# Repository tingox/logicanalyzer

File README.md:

# LogicAnalyzer

test 

## Downloads
You can find all the compiled projects in the [Releases section](https://github.com/gusmanb/logicanalyzer/releases).

Latest version: Release 5.1.0.0, 05/05/2024
----

# More boards on the go!

One of the new functionalities of the RP2350 is the capability of having two XIP devices and also has the full device implementation (RP2040 only had READ capabilities implemented). This means that is possible to have (for example) a flash device *and* a PSRAM connected to it.
Unfortunatelly the Pico 2 does not expose the QSPI pins and they are tied directly to the flash... But there is hope! PiMoroni has developed the PiMoroni Pico Plus 2 which contains 16Mb of flash and 8Mb of PSRAM.

I already have ordered one of these new boards and have some ideas on what could be done with them :D
Right now the most possible one is this: PSRAM is not fast enough for sampling at a decent speed with many channels, BUT, it is fast enough for something like storing ADC samples, so what I'm going to try is to allow the mix of analog and digital channels. The analog channels will be very slow compared to the digital ones (only 500Ks/s) but it still can be useful to monitor behaviors of things like motors, servos or whatever. As the PSRAM is 8Mb it will allow to store up to 8 seconds of analog data on single channel mode (2 bytes per sample at 500Ks/s is roughly 1Mb/s of data), this, combined with the upgraded onboard ram and the burst mode can be really useful in multiple projects.

Stay tuned for more news!

----

# Exciting news! The Pico 2 is coming soon!

As some of you may know the Pico 2 is being released this month. The new Pico 2 is a very exciting upgrade of the pico, more powerful cores, two alternative RiscV cores, three PIO units instead of two and 520Kb of RAM!

This can be a game changer for LogicAnalyzer, only with the new ammount of RAM the quantity of samples is going to increase massively, we're talking about three times the current ammount of samples!

Also, there are really exciting changes on the PIO side, the new IRQ system allows to intercomunicate the PIO units, this means that the trigger pins could be freed now, and this, as small change as it seems can be really amazing combined with the new third PIO unit... Think about this, a 64Mb dual SPI RAM running at 100Mhz connected to the two free pins and controlled at full speed by the third PIO unit... 

I was preparing a release for this month but it's going to be delayed, once I receive the new Pico's I will start the development for the Pico 2 and once it's completed I will release all at once.

Stay tuned!

## RELEASE 5.1

This release is a QoL release with some functional corrections. For more details check the release page.

## RELEASE 5.0, Burst mode is here!

New release with exciting feature!

The biggest change on this release is the Burst mode. With burst mode you can capture blocks of data and the analyzer will rearm itself immediatelly and capture more data when the trigger condition is met again. This will improve the memory usage discarding unneeded samples! Right now only the simple trigger mode accepts burst mode but in a future I will try to implement it in all the other triggers.
For more information check [the wiki.](https://github.com/gusmanb/logicanalyzer/wiki/06---The-LogicAnalyzer-program#triggers)

Also new features to ease the navigation in the capture viewer have been added like shortcuts and a preview of the full capture. More info in [the wiki.](https://github.com/gusmanb/logicanalyzer/wiki/06---The-LogicAnalyzer-program#navigating-on-the-capture-viewer)

Finally multiple improvements have been done, some bugs in the capture tail detection have been corrected, the USB transfer has been improved using directly the CDC transfer functions and more.

Beware that this version is not compatible with other ones, the protocol has changed. The driver will check the device version and will not connect to it if it is lower than V5.0.

Have fun!

----

## UPDATE 28/06/2023 - Release 4.5.1 - QOL improvements

This release include some QOL updates to the applications.

LogicAnalyzer app:

* Ammount of on-screen samples will be preserved if you repeat the last capture.
* Added a new menu entry called "Repeat las analysis" to the protocol analyzers, it will execute the last analysis performed to speed up things.
* Changed where config files are stored, they will use the %appData% folder now ($home/.config in Linux).
* Changed horizontal scrollbar visibility.

CLCapture app:

* Now channel names can be provided from the command line.

Have fun!

----

## UPDATE 11/04/2023 - Release 4.5 - Support for the RP2040-Zero and new board definition system

This release includes only an update to the firmware.

First, the RP2040-Zero is now officially supported (no shifter board for it though). 
You can download the firmware for it on the [releases](https://github.com/gusmanb/logicanalyzer/releases) section. Also, the pinout has been added to the [wiki](https://github.com/gusmanb/logicanalyzer/wiki/02---LogicAnalyzer-Hardware#barebones-configuration) so you can use it with the bare-bones configuration.

And second, the firmware has been refactored in order to make a lot easier to add new boards. You have the complete instructions on how to add support to a new board on [the wiki firmware section](https://github.com/gusmanb/logicanalyzer/wiki/03---LogicAnalyzer-Firmware). Also, as some boards include the very popular WS2812 RGB led the firmware includes a driver for it, it's purely software-based, no timers nor interrupts needed, so feel free to use it if you want.

If you add support for a new board, feel free to create a pull request with the changes :)

Have fun!

----

## UPDATE 25/02/2023 - Release 4.0 is up! Channels a go-go!

Hi again! This is a BIG update loaded with new functions and improvements to the hardware, firmware and software!

Let's start with the little things: we have a logo! Yes, it's nothing important but I hated to not to have a proper one so I designed one that I think fits well to the project :D

Next, we have a proper Wiki! All the project has been documented: hardware, firmware and software. If you have any doubt check it as I have tried to explain everything related to the analyzer usage in there. If you find any error or missing feature please open an issue and I will correct it as soon as I can.

Ok, now the changes to the hardware. There is a new pcb for the analyzer that includes two connectors to daisy chain the analyzers. You can use two or three Dupont wires (the central pin is unused, it's reserved for future usage, I have left it there so anyone that produces these PCB's can patch them easily).

And the firmware has also been updated to support the daisy chaining. So, what is for the daisy chaining? Well, daisy chaining allows to chain up to five analyzers without wasting pins so you now will be able to capture a massive ammount of **120 CHANNELS!!!** Check the [Connection](https://github.com/gusmanb/logicanalyzer/wiki/06---The-LogicAnalyzer-program#connecting-to-devices) and [Capture](https://github.com/gusmanb/logicanalyzer/wiki/06---The-LogicAnalyzer-program#capture) sections of the Wiki to know all the possibilities and how to use them.

Now, the software. It contains many changes, so I'm going to start with the improvements and then with the new functionalities.

First I have improved the sample rendering. It is now more visible and looks a lot better. Also, the guides shown to see where a sample starts and ends are automatically scaled or removed, it made no sense to have so many lines that they made a solid gray background, so when there are too many they will get automatically deactivated. Also, this allowed to improve the performance so now the sample viewer will allow to show up to 2000 samples in screen without any check.

Related to this the protocol analyzer renderer has been updated, it will take less useless space and will hide the information if it does not fit in the assigned space.

Now, the connection system has been updated to include a "multidevice", this is the device that you must use when using the daisy chained analyzers.

Next, the capture dialog has been updated, the mode selector has been removed and the mode is autoselected based in the channels enabled, check the [Wiki page](https://github.com/gusmanb/logicanalyzer/wiki/06---The-LogicAnalyzer-program#basic-parameters) to know the limits and modes.

Also, the capture dialog has a new channel selector, more visual and that includes the name field for the channels, instead of configuring the names after the capture has been finished (and lose these if you capture again) the names can be entered directly on the capture dialog. These names will be preserved between captures (and if you change them from the channel viewer these changes will be respected).

This new channel selector also allows to show up to the 120 channels that can be used when daisy chaining five devices, the selector will have a scrollbar when the channel list is bigger than its space.

Another change, the editing features have been improved and expanded. First of all, you will not need to create regions to execute edit actions, the sample range selection has been improved and it is used now for these. Check the [Wiki page](https://github.com/gusmanb/logicanalyzer/wiki/06---The-LogicAnalyzer-program#editing-captures) to see a description on how it works and which new features have been included.

Finally, the system now can create capture files from scratch, for this I have implemented a language that allows to describe signals in an easy way, it even includes a colored syntax editor, check the [Wiki](https://github.com/gusmanb/logicanalyzer/wiki/06---The-LogicAnalyzer-program#the-signal-description-language) for a description of this language!

Also, I already have planned the next update, I'm not sure when it will be ready but I will implement it for sure, and this is one of the motivations to create the SDL language: replay captures! ;)

This is a resume of the most prominent changes, surely that I forgot some, but all are documented in the Wiki, so ensure to review it!

Any feedback about the update will be welcome, so don't hesitate to open issues or start discussions.

Have fun!

## UPDATE 07/02/2023 - New release with updated shared driver.

This is a bug-fix release, with the introduction of the Pico-W WiFi support I unified the transfer mode in the driver using streams for network and for the serial port, but I forgot that .net 6.0 Ports package causes problems with Linux, so the previous release will hung the app when receiving more than 4k samples... Doh!

I have updated the code to use the same work around that I used previously and the problem has been fixed.

Have fun!

----

## UPDATE 04/02/2023 - New release! Bugs corrected and more samples!

Hi! This update comes loaded of news.

### First of all, bug corrections. 

The biggest bug that has been corrected is the fast trigger in the Pico-W. When I implemented the Pico-W I tried it extensively, but I used only the simple trigger to do the tests. What was my surprise when I tried to use the Pico-W with a fast trigger and I found that it got completelly hung!

The thing is that the Pico-W hides a little secret that I haven't found documented anywhere, this little secret is that the driver uses a PIO program to do the transfers! The fast trigger uses a full PIO unit, all its 32 instructions to create a jump table, and the CYW driver uses a SM in the PIO1 to do the SPI transfers. So I tried to swap the PIO units and it at least started to capture, but the capture was never finished, I have revised up-to-down the driver and still haven't found why the PIO1 interrupts don't work at all after the CYW driver has been enabled, so I have done a work-around that does not need the IRQ to trigger a handler. So, if you are using a Pico-W update the firmware asap.

The next bug is a small bug that caused that some samples weren't clear correctly when a trigger was rised immediately after starting capture (for example the trigger condition is already met when the first sample is done).

### And now, the really big news, MORE SAMPLES!

I have tweaked the buffer transference between the PIO and the memory and it allows to hold up to 131071 samples! Of course this is at the expense of how many channels you use, the device now has three modes: 8 channels, 16 channels and 24 channels.

The sample limits are specified here:

 * Mode 8:
 
     * Minimum pre-samples: 2
     * Maximum pre-samples: 98303
     * Minimum post-samples: 512
     * Maximum post-samples: 131069
     * Maximum total samples: 131071
     
 * Mode 16:
 
     * Minimum pre-samples: 2
     * Maximum pre-samples: 49151
     * Minimum post-samples: 512
     * Maximum post-samples: 65533
     * Maximum total samples: 65535
     
 * Mode 24:
 
     * Minimum pre-samples: 2
     * Maximum pre-samples: 24576
     * Minimum post-samples: 512
     * Maximum post-samples: 32765
     * Maximum total samples: 32767

As you can see, using the 8 channel mode you can capture up to four times the samples that were available until now, a substantial increase.
The channels used for 8 and 16 modes must be the first ones, you cannot choose eight random channels, and this introduces a limitation, they collide with the complex and fast triggers (not the simple trigger, for that you still can use any channel left). Bear in mind this to plan how you configure your capture, for example for the 8 channel mode you still can have a 8 channel complex trigger or a fast 5 channel trigger without including these channels in the capture, but if you need more channels for one of these triggers, or you need to use the 16 channel mode you will suffer of this.

### Another new update, now you can show up to 1024 samples in screen!

You can activate this feature from the main screen, it has a checkbox (which will warn you as this may be a very CPU intensive task for old computers) that allows you to change the on-screen samples from 200 to 1024, this is really useful for use with big screens and modern computers.

Also I have tweaked a bit the appearance of the sample viewer, I didn't liked the dashed lines so now all are continuous ones.

Well, that's it for now.

Have fun!

----

## UPDATE 03/02/2023 - Measurement tool.

This is a very handy update to the analyzer, you can measure a region and get information of each channel: total samples selected, period of the selection, number of positive pulses, number of negative pulses, average and predominant period for positive and negative pulses and average and predominant frequency.

The predominant values are calculated applying a variant of the 95th percentile rule to discard aberrant/broken samples and I must say it works really well, it matched exactly all the frecuencies I have tested.

There is still no new release, you will need to compile the application if you want it, but I will create the release very soon.

Have fun!

----

## UPDATE 02/02/2023 - I2C protocol analyzer.

New day, new analyzer :D. This time is the turn for I2C. The analyzer will show you the raw data, the ACK/NACK's and will also show the device address (7 and 10 bit modes), operation of a request and any kind of frame error. To install it get it from [here](https://github.com/gusmanb/logicanalyzer/blob/master/I2CProtocolAnalyzer.dll) and copy it to the "analyzers" folder of the application.

Have fun!

----

## UPDATE 01/02/2023 - Serial protocol analyzer.

This is a small update, I have created a serial protocol analyzer (RS-232). This update does not include a release but I have left the analyzer library compiled in the repository. To install it get it from [here](https://github.com/gusmanb/logicanalyzer/blob/master/SerialProtocolAnalyzer.dll) and copy it to the "analyzers" folder of the application.

It supports positive and negative polarity (for TTL and RS-232 level signals), two channels (RX + TX), 7 or 8 bits, no parity/odd parity/even parity and 1, 1.5 or 2 stop bits.

Have fun!

----

## UPDATE 31/01/2023 - Pico-W support and WiFi!

It's finally here! WiFi support!

First of all, there are now three different firmware versions in the release section, one with no suffix for the regular pico, another with the "W" suffix for the Pico-W with no WiFi support and a final one with the "WIFI" suffix for the Pico-W with WiFi support. Choose the one that best suits your needs.

Now, how to use the WiFi support?

First of all, you need a Pico-W, I think that's obvious :D, flash it with the "WIFI" firmware and the device is ready to be used. If you plan to solder the Pico-W to the analyzer board beware to not to add the debug pins as they are now located in the middle of the board and it will not allow you to solder it, if you want them then you will need to use some pin headers to rise the Pico from the board (for my own device is what I always have done, in this way I can replace the Pico whenever I want).

Ok, now let's see how to use it.

First of all, you need to connect at least once the Pico-W to the computer to configure the network settings, this process can be done as many times as you want, connect the Pico-W to the computer and use the CLCapture or the LogicAnalyzer software to configure it.

When you connect the Pico-W with the WiFi firmware you will notice that a new menu gets enabled:

From there you can then select the "Update Network Settings" menu.

That will open the dialog to configure the network settings, you must enter the SSID of your router, the password (only WPA2 is supported), the desired static IP address and the listening TCP port.

Once these are configured accept them and they will be saved to the Pico-W flash, immediately the Pico-W will try to connect to your router, if it's available it will connect and it will be available for network connection.

To connect to the Pico-W through WiFi you must select from the dropdown menu the "Network" option.

Once you select it and press the "Open" button the network connection dialog will open.

Fill the IP address and port and press "Accept", if the device is available it will connect to it.

And that's it! From that point the device works exactly as before, for the application is indifferent if it is connected through network or USB, it has the exact same functionalities.

### The CLCapture updates

The CLCapture also supports the network connection and configuration, for that purpose now the command line starts with a verb, execute the program without any parameter to check the verbs and only with a verb to get the required parameters.

### Some notes

Both interfaces (USB and WiFi) work at the same time, but when a client gets connected through WiFi the USB will be ignored until the client gets disconnected, keep it in mind.

I have found some quirks on the Pico-W WiFi support, the first one is that it does not support at all to connect without a DHCP server, and it always gets the network information from there, fortunatelly I have found a way to change the IP address once it is connected to the AP. This also causes a problem (at least in my router), if you are already connected to the AP and you change the network settings the device disconnects from it and reconnects with the new info, if is the same AP (per example you have just changed the IP address) the static IP is ignored and it will retain the one assigned by the DHCP server, the solution is easy, restart the Pico-W and it will connect with the new IP address.

The firmware now has three "flavours" when compiled, this is controlled from the "LogicAnalyzer_Build_Settings.h" header and the "CMakeLists.txt" files, both contain instructions on how to change the settings based on your preferences.

A user adviced me that the Pico-W may have problems if the USB is connected to a host and the WiFi is used. I haven't experienced none of these and I have tested it extensively, maybe as I have used a sepparated core for the WiFi it avoids this kind of trouble, but if you experience them then use a USB power supply (like a phone charger or similar) if you want to connect through WiFi.

### The future

I'm thinking about creating a new PCB board that contains a battery and an USB charging module, in this way the device will become totally free of wires (except for the ones for the signals, obviously). I think this could be extremely useful, you will be able to place the analyzer even inside a computer or any kind of device and connect to it remotely, I think this could be extremely useful for devices that are in fixed places or are big and difficult to move (like old mini computers or car ECU's).

Stay tunned for more news, and be sure the project still is not completed!

Have fun!

----

## UPDATE 29/01/2023 - Software update

This release contains many updates to the GUI, CLI and driver and also includes many new target architectures.

### Updates to the GUI

First, the sample viewer and sample marker contains also the half of the cycle (where the sample was done in the cycle) to make it easier to see the data.

Now you can create a "user mark", it is a temporary mark and is not saved with the save/export data, just an useful tool to see things. Click on the sample marker without dragging and you will set the user mark place. To remove the user mark click again in the same spot.

Deleting samples is now possible, when you right-click on the sample marker over an existing region now instead of deleting the region it will pop a menu which will allow you to delete the regions that were under the mouse or to delete the regions *and* the samples.

Added more meaningful error messages, in any case the limits in the numeric up/down controls have been updated to match what the driver expects.

### Updates to the CLI

It also includes the new messages with more meaningful errors.

### Updates to the driver

The driver has been adjusted to give more flexibility in the pre/post samples, the valid parameters now are:

    -Frequency must be between 3.1Khz and 100Mhz
    -PreSamples must be between 2 and 31743
    -PostSamples must be between 512 and 32767
    -Total samples cannot exceed 32767
    
Have fun!

----

## UPDATE 17/12/2022 - Application repackaging

One of the features that I loved for .net when it was introduced is the ability to create applications that does not require the user to install the .net Framework independently. I always prefer to create portable packages, something that you uncompress wherever you want and it just works. This creates a bit bigger applications but nowadays with the massive storage devices we have and the fast Internet we have this is not a problem, while having to install the framework can be painful in some cases (restricted user privileges environments, problems with old .net installations, etc).

Well, thanks to the people at [Laboratoire Ouvert Grenoblois](https://www.logre.eu/) I found that the packages for unix/macos where incorrectly packaged and didn't included the framework and needed its installation... Doh!

I have re-packaged all the applications (CLI and GUI) and now all the versions include the required files, it should not need any more the installation of the .net framework.

Also, I have bumped up the firmware to the version that includes the new tail detection (beware, it will still inform that is the V1.0, I will correct the version numbering with the release of the Pico-W support).

Note: If you already have the applications and they are working ok for you that means that you already have the framework installed and there is no need to download the new packages, you only need these if you're doing a new installation or you had problems with the previous versions because the missing framework.

Have fun!

----

## UPDATE 12/12/2022 - Working towards Pico-W support

One of the goals that I want to achieve with the analyzer is to support the Pico-W. Would not be great to have a battery powered analyzer that connects to your computer via WiFi? For me at least this is a really desirable option as I have my main computer on a different desktop than the electronics bench, so when I want to analyze signals I must have a long USB cable hanging from the computer to the analyzer or I must do the analysis in the computer desktop. Also even if you are in the same desktop the less cables that you have around the easier is to work. For this, the Pico-W is ideal, as the analyzer does not transfer data in real time it does not need an extremely fast connection, for transferring the data once it has been captured the integrated WiFi of the Pico-W is more than enough.

### Pico-W missconceptions

It has been a while since I got the Pico-W and I didn't had enough time to start really digging on how the thing works, so my previous knowledge about the W was based on the first notes that were released to the Internet (I bought it at release day). Something that was stated in many places was that the W used some GPIO's to control the WiFi module so you would have less available IO's for your usage.

I have been really pleased when I have read by myself the datasheet and how the Pico has implemented in reality the WiFi module. It indeed uses some GPIO's to control the WiFi, but, those GPIO's have never been available to the user as regular GPIO's. The Pico uses GPIOs 23, 24, 25 and 29 for internal usage (LED, VBUS sense, etc). So, what have they done in the Pico-W to not to use additional GPIO's? They have lifted those functions to the GPIO's of the WiFi module. The WiFi module itself contains a GPIO port and now that port is the one that contains those functionalities, so now GPIO's 23, 24, 25 and 29 control the WiFi module and the first three GPIO's of the module are used for those functions.

So, what does all this means for the analyzer? Well, it means that very little changes needs to be done in the capture code and only the front-end code needs to be changed. Also, this means that the W version will also retain all the 24 channels, it will not lose any capability. Wohooo!!!

### Changes to the capture code

As all the GPIO's that are used to capture are the same there is no need to change any code except for one very small part, the "end capture" mark. The PIO always capture pins in a sequential way, it means that you cannot have "holes" in the pin sequence, and to get the full 24 channels every single available GPIO must be used, up to GPIO28. This means that the GPIOs that controlled the LED's, VBUS and so on also are captured but ignored. Said that, to mark where the capture was finished in the buffer a special value that was impossible to happen was added after the last capture, it was based on that the device those GPIOs would never be 1's. In theory, as we are capturing 32 bit words there will always be some zeroes at the tail, but I'm paranoid and also it is not elegant, so I decided to modify the tail detection code.

Instead of basing the tail detection in a mark in the buffer (which requires to iterate the buffer until it is found) now the tail detection is based in the DMA channels transfer state. This was my original idea, but unfortunatelly the Pico API does not expose a direct way of reading how many transfers have been done or how many are left, you can set them but cannot read them, so I abandoned that idea.

This time I have digged a bit more and went directly to the RP2040 datasheet and it states very clear that the TRANSFER register is R/W, so you can read how many transfers are left. I have no idea why the API does not expose it, but knowing that is very easy to access directly to the register using the dma hardware channel structure.

Now what the code does is: once the capture has finished before aborting the DMA channels it checks which one is busy (remember, there are four DMA channels in a ringed chain, so only one DMA will be busy, the one that's waiting for the next transfer from the PIO), checks how many transfers are left and based on the DMA channel number and the transfers left it computes the index of the last capture.

This is more elegant, faster and prevents that my paranoid side rings a bell each time I see that code thinking on the Pico-W, so all are advantages :D

### Wanna try it?

In the repo source under the [build](https://github.com/gusmanb/logicanalyzer/tree/master/Firmware/LogicAnalyzer/build) folder you will find the UF2 file with the new detection code, so you can try it with the Pico-W, it will still use the USB to transfer the data but you can check its compatibility. I still haven't got time to try it in the W but I plan to do it soon. In any case, if you test the new firmware in a W or a regular Pico I would be thankful if you can leave a comment telling your experience, if you have found any problem or if it worked as expected.

### Next steps

Well, the next step will be to add the front-end code for the W, the idea is to have a single project that based on settings compile it for the W or for the regular pico. About how to implement it, I still need to check the W API for the WiFi, but one thing that I want to do for sure is to have the WiFi module off when the capture is running to avoid any kind of glitch because interferences, I fear that the traces may act as antenna and read false data, so I'm thinking that I will use UDP instead of TCP, use a broadcast address to send/receive data and as UDP does not require an stablished connection it will allow to shut down the module without breaking the network. In any case these are my first thoughts and may change once I start implementing it.

Have fun as always!

----

## UPDATE 27/11/2022 - Small changes, great value

I have uploaded a new version of the PCB's and the firmware. It contains a small modification which can give great value to the device.
Do you have an oscilloscope? Have you ever wanted to trigger it based on the value of a data bus? Or when some digital signals take a concrete value?
Now the logic analyzer offers this functionality!

The modification is very simple, the GPIO pins used for the complex/fast triggers have been exposed through a diode and that signal can be used to trigger other devices like an oscilloscope. Or even you can chain multiple logic analyzers to have as many channels as you want! Configure your analyzer for a complex or fast trigger, connect your device to one of the EXT pins (and GND as needed) and start the capture. To chain multiple analyzers you must configure a simple trigger and connect one of the pins on the secondary analyzers to the EXT trigger pin. In the future and if it is requested I will add another capture mode for the EXT so it can chain more than 3 analyzers.

There is a small delay from the trigger to the signal, I have measured it and it is a delay of 20ns for the fast trigger (the two cycles that takes to detect and propagate the trigger condition) and 35ns for the complex one. Also, the diode introduces a small delay of 4ns, if you want to remove that delay you can skip the diode and the pull-down resistor and place a bridge where the diode should be placed, but be ware that you will leave the trigger unprotected against polarity inversions.

The external trigger has been routed to two pins, in this way you can chain as many analyzers as you want, or connect two other devices.

The new pinout is this:

Beware to not to use a new analyzer with an old shifter board, it has been also modified to include the ext signals, if you use an old sshifter with a new board you will create a short between +v5, +3.3v, GPIO0 and GPIO1 what will be fatal.

For the new shifter the pinout is the same as the analyzer but the +5v pin is the +5v/ext_ref depending on the jumper setting.

Finally I also have updated the firmware to disable the GPIO synchronizers what reduces other 4ns of delay.

Have fun!

----

## UPDATE 03/09/2022 - Abort captures
Minor release adding the capability to abort a running capture. To use this feature you will need to update the firmware and the application.

----
## UPDATE 27/08/2022 - LevelShifter update and more...

I have updated the level shifter board. It's a minor change but it makes the shifter a lot more flexible as now you can use the internal +5V as reference for the input voltages or you can use an external voltage source as reference. Basically this allows you to use the target device's voltage sources as VRef so the board now can work with levels between 1.65v and 5.5v

New board:

To use an external VRef source you need to remove the jumper JP1 and connect the external voltage reference to the +5v/ExtVRef pins of the input header.

BEWARE!!! There is no overvoltage protection for the VRef input so you must be careful to respect the 5.5v maximum voltage limit.

#### More things to come very soon:

- Capability to abort a running capture (under testing)
- Enclosure for the analyzer (a preview is already in the repository, do not use as I'm on the process of adjusting it)

Enjoy it!

----
## UPDATE 31/07/2022 - RELEASE 2.0

Good news! The multiplatform application is ready!

The application has been completelly rewritten using AvaloniaUI, it works in Windows, Linux, Linux-ARM (Raspberry) and MacOSX.
It has been tested under Debian, Raspbian and Windows 10, MacOSX has not been tested as I don't have a working mac but it should work without problems.

Also, the new app includes improvements over the original one, like the ability to export the captures to Sigrok and better performance in general.

Application running in Windows:

Application running in Linux:

Application running in Raspberry:

----
## UPDATE 13/07/2022

I have managed to finally test the command line application in Linux and it worked as expected so I'm releasing it.

The command line capture program is a multiplatform command line application, it has versions for Linux, MacOSX and Windows and allows to capture data directly to a CSV file. The file format is compatible with Sigrok/PulseView so you can analyze the captures with it.

NOTE FOR LINUX/MACOSX USERS: Due to how I compile the apps you will need to make the app executable with CHMOD.

The app has been tested in Linux and Windows, if any user tests it on MacOSX please leave an issue with the results, I will be very thankful :D

### How to use the command line app:

If at any moment you need help you can execute `./CLCapture --help` and it will show you the usage help.

The app requires seven parameters to start a capture: serial port, sampling speed, channels to capture, pre-trigger samples, post-trigger samples, trigger definition and output file name.

- The first parameter is the name of the serial port of the logic analyzer.
- The second parameter is the desired capture speed in samples per second.
- The third parameter is a list of channels separated by coma, per example `1,2,3,4` or `1,16,24`.
- The fourth parameter is the number of samples to capture before the trigger.
- The fifth parameter is the number of samples to capture after the trigger.
- The sixth parameter is the trigger definition expressed in the form of: "TriggerType:(Edge, Fast or Complex),Channel:(base trigger channel),Value:(string - containing 1's and 0's indicating each trigger chanel state)". Per example, if we want an edge trigger on the positive edge using channel 4 the value would be `TriggerType:Edge,Channel:4,Value:1`. If we would want a fast trigger using channels 3,4,5 and a pattern of "101" the trigger definition would be `TriggerType:Fast,Channel:3,Value:101`. Note that there are no spaces, each parameter is separated by coma and no quote is used.
- Finally the seventh parameter is the output file name we want to generate.

A complete example to capture channels 1, 2, 3 and 4 at 100Mhz using channel 5 as positive edge trigger and storing the results in a file called "output.csv" would be similar to this:

```./CLCapture /dev/ttyACM0 100000000 1,2,3,4 512 1024 TriggerType:Edge,Channel:5,Value:1 output.csv```

If everything goes Ok you will see something like this:

```
Opening logic analyzer in port /dev/ttyACM0...
Conneced to device LOGIC_ANALYZER_V1_0 in port /dev/ttyACM0
Starting edge triggered capture...
Capture running...
```

The analyzer will blink while the capture is running and once it has finished it will print the result:
```
Capture complete, writting output file...
Done.
```

This capture will contain the data in CSV and is compatible with PulseView. To import it in PulseView go to "Open->Import comma-separated values...". The file is generated in a way that you don't need to change any of the CSV paramters, you will need to specify only the number of channels and the capture speed.

Once imported you will see your data, something like this:

I hope that with this, at least until the multiplatform app is ready, all the users can use the analyzer the way they want, it will work in all the common OS'es and it introduces compatibility with Sigrok/Pulseview in a way that is not intrusive for Sigrok nor for the LogicAnalyzer app.

Have fun!

----
## UPDATE 12/07/2022

I have received the shifter PCB's and there is an error. The footprints of J1 and J2 are exchanged, so what should be inputs are outputs and vice-versa. Thankfully this is not a problem, as the PCB is completelly symmetric and it has components in both sides flipping the board fixes the problem.

Board before flip.

Board after flip.

The KiCad project is already updated.

The good news is that the board works like a charm, I have tested it with my clock generator with a 50Mhz clock and it captures every single half cycle perfectly, like if the board was not there :D

So if you want to build your own shifter board, it's ready and tested.

----
## Description
Cheap 24 channel logic analyzer with 100Msps, 32k samples deep, edge triggers and pattern triggers.

----
## Overview
LogicAnalyzer is a very cheap analyzer based in a Raspberry Pico. The analyzer offers up to 24 digital channels, pre and post trigger sampling, edge trigger and pattern trigger up to 16 bits.

The most basic version is purely a Pico as-is, you only need to short GPIO0 and GPIO1, upload the firmware and you're good to go.
Of course this has some limitations as the Pico only supports 3.3v, if you want to use it to diagnose 5v signals I also have designed a fast level shifter board.

Additionally to the hardware the logic analyzer also includes a powerful software (Windows only for now) where you can visualize the captured data, export captures, use protocol analyzers, etc.

## About logic analyzers and triggers

A logic analyzer only cares about logic states of lines, so without thinking much about it you may think that any microcontroller using DMA channels that read GPIO values would be more than enough, but that is the "easy" part of a logic analyzer, the problem comes when you need to trigger the captures based in GPIO states and you want also to have data captured previously and after the trigger happens.

For that, you need to compare the read values from the GPIOs check if the pin or pins values match the requested trigger and you must do it as fast as you want to capture, so for example, the most basic comparison will at least consume 3 or 4 instructions, if each instruction is 1 to 4 cycles (more or less, I'm thinking in ARM processors) then you will use up to 16 cycles to read a sample, so you would need a 1.6Ghz CPU to sample at 100Msps.

So, how the heck the pico is able to achieve this? Well, the key are the PIO units, these units are a wonder, they are coprocessors explicitly designed to handle IO, it uses a very restricted and deterministic assembler (only nine instructions that each take a single cycle to execute) but extremely efficient, so efficient that with only two instructions is possible to create a loop that captures GPIO data up to 30 bits and redirects the program flow based in the status of one of these GPIOs.

Of course there are some limitations, that two-instruction loop can only change the execution flow based on a GPIO pin, it can't branch based on a pattern (using only two instructions) but as we have more than one unit (each pico has two units and each unit has four state machines, so you can run in parallel up to 8 programs) we can abuse a bit the system and create a separate trigger program that notifies the capture program using a pin, that's why GPIO0 and GPIO1 are shorted.

The analyzer described here has three trigger modes: edge trigger, fast pattern trigger and complex pattern trigger.

The edge trigger uses a single program, that's the basic version that uses only two instructions, runs up to 100Msps and the triggering is synchronized with the captures.

The complex triggers is the first that uses two programs, one to capture and other for the trigger. The complex trigger supports patterns up to 16 bits matched from consecutive channels in the first 16 ones.
Having two programs is key to keep sampling up to 100Msps, the trigger program uses three instructions so its speed is limited to 66Msps, but the sampling can run at full speed using two instructions. Of course this presents some inconveniences, there is latency between the trigger signal and the reported trigger, also if the trigger pattern lasts less than one cycle at 66Mhz the trigger can be lost, and finally as the trigger always runs at maximum speed on lower speeds there may happen a "glitch", the trigger is raised because the pattern was found but the sampling program does not register this as it runs at a lower speed.

Finally we have the fast trigger, this uses a very clever "hack" (thanks to alastairpatrick from the Raspberry forums for the idea) that abuses the limitations of the PIO units. Each PIO unit can handle only 32 instructions, so the program counter of a state machine rolls to 0 if it's overflown, also the PIO assembler has an instruction to MOVe data from the IN pins to the program counter, and finally the PIO assembler allows to modify pin values on each instruction without using any extra cycle. So, said that, the trick consists on create a full 32 instruction program that moves the values from the GPIO to the PC and the instructions that are allocated in indexes that match the required pattern block the execution and sets a GPIO to 1.
Of course this limits the possibilities for the pattern, we can use up to 5 channels for this trigger but the trigger will run at full speed (it can work even faster, up to 200Msp).

If you want more info about the triggers check the PIO code in the source as there is more explanation on how this works.

## Schematic

The base schematic is only the Pico with a short between GPIO0 and GPIO1 but I have designed a PCB for convenience, it has been designed to maintain trace lengths so no glitch may happen because propagation delays (at 100Mhz it should not be a problem, but in marginal cases if there is a noticeable trace length difference some picoseconds of delay can be introduced and change the analyzed values).

Also, as the Pico only supports 3.3v I have designed a level shifter board, it uses very fast transceivers (TXU0104) which met the 100Msps specifications.

ATTENTION! I'm in the process of receiving the PCBs so they are not tested, I will update this document after testing it.

## PCB

There are two PCBs, one for the analyzer and other for the level shifter.

## Building the firmware

To build the firmware you need to have an environment configured for Pico development, but if you don't have it don't worry, the releases include the UF2 file, so you only need to start the Pico in program mode, drop the UF2 file to the Pico drive and that's it, you have a Logic Analyzer ready to be used.

## The software

Before designing my own analyzer I have used some cheap Chinese analyzers and all use the same software, OLS, OpenBench Logic Analyzer, and to be honest, I don't like it. So, I have implemented my own binary protocol (more info in the firmware code) and visualization software. 

This is a .net desktop program for Windows (if I have enough requests I may plan to create a .net MAUI version that runs in Windows/MacOS/Linux) which allows you to visualize the capture data, highlight sampling ranges, name channels extremely fast, export the captured data preserving the capture settings and ranges, implements protocol analyzers (and a very easy system to include your own ones) and so on.

For now I have already implemented a SPI protocol analyzer but I plan to implement also I2C, RS-232 and system bus analyzers (for old computers, 16 address bits and 8 data bits). In any case, with little knowledge of C# you can add your own protocol, which makes the program capable of analyze proprietary protocols.

The capture interface is straight and self-explanatory, and the software preserves your last settings, can import settings from exported captures and allows you to re-issue a capture without having to go through the configuration process.

## Build requirements

To build the firmware you will need a build environment for the Pico-SDK version 1.3.1 or newer. For Windows users I recommend to use the [Pico-Setup project](https://github.com/ndabas/pico-setup-windows/releases).

To build the application you will need [Visual Studio 2022](https://visualstudio.microsoft.com/) with the C# language installed.

## Using the device

The device once connected to your PC will be detected as a serial port, no drivers are needed. Once you open the software you will have a list of serial ports and you must choose the correct one, once selected if you "Open" the device it will show the firmware version in the top section and will enable the capture buttons.

To use the analyzer connect the required channels to the signals you want to analyze, also connect at least one ground pin from the Pico to the analyzed device, press the "Capture" button, configure your settings and start the capture. The Pico will start flashing until the trigger condition is met and the capture will run.

Once the capture has finished you will see the channels, a range of up to 100 samples and the trigger event will be right at the left side of the sample area.

To name your channels you have a grey box under each one, these are textboxes where you can set whatever you want, and if you export your capture they will be preserved.

To create an highlighted region press over the numeric top bar and drag to select how many samples are highlighted.

This will open the region creation dialog where you can choose a name for your region, the color and the opacity of the highlight.

If you want to delete a region press on the numeric bar over a highlighted region and it will be deleted. Regions are also exported with captures.

## Adding custom protocol analyzers

To add a new protocol analyzer you need to create a .net 6.0 assembly that references the LogicAnalyzer assembly and implements at least one class based in "ProtocolAnalyzerBase". Basically you will provide a list of settings to present to the user and then you will implement an analysis function that returns analyzed channels.

Each analyzed channel will specify a list of segments where data is overlayed (to present data to the user) and also it may provide a custom renderer for the data segments. You can create your own custom renderers or just provide an instance of the already included "SimpleSegmentRenderer".

---

## About Sigrok and the custom app

I have been reading some comments about why create my own application and why not use Sigrok as it would have been developed faster. First of all, the full project including firmware, PCB's and Windows client took me less than a week of development, I have been creating Windows apps for more than 20 years and it takes me less time to implement a rendering system, plugins and so on than implementing a third-party driver :)
In any case, my main reason to not consider to use sigrok is because I tried to use it with some cheapo analyzers and on my machines it simply would not run, I'm not sure if some component that I use for development is incompatible with it but on my three machines it crashed, in one machine it does not open at all and on the other two I had random crashes when I tried to capture data.

In any case, I will try to get it running in one of my development machines and if it works I will check how complex would be to create a driver for it.

---

Have fun!

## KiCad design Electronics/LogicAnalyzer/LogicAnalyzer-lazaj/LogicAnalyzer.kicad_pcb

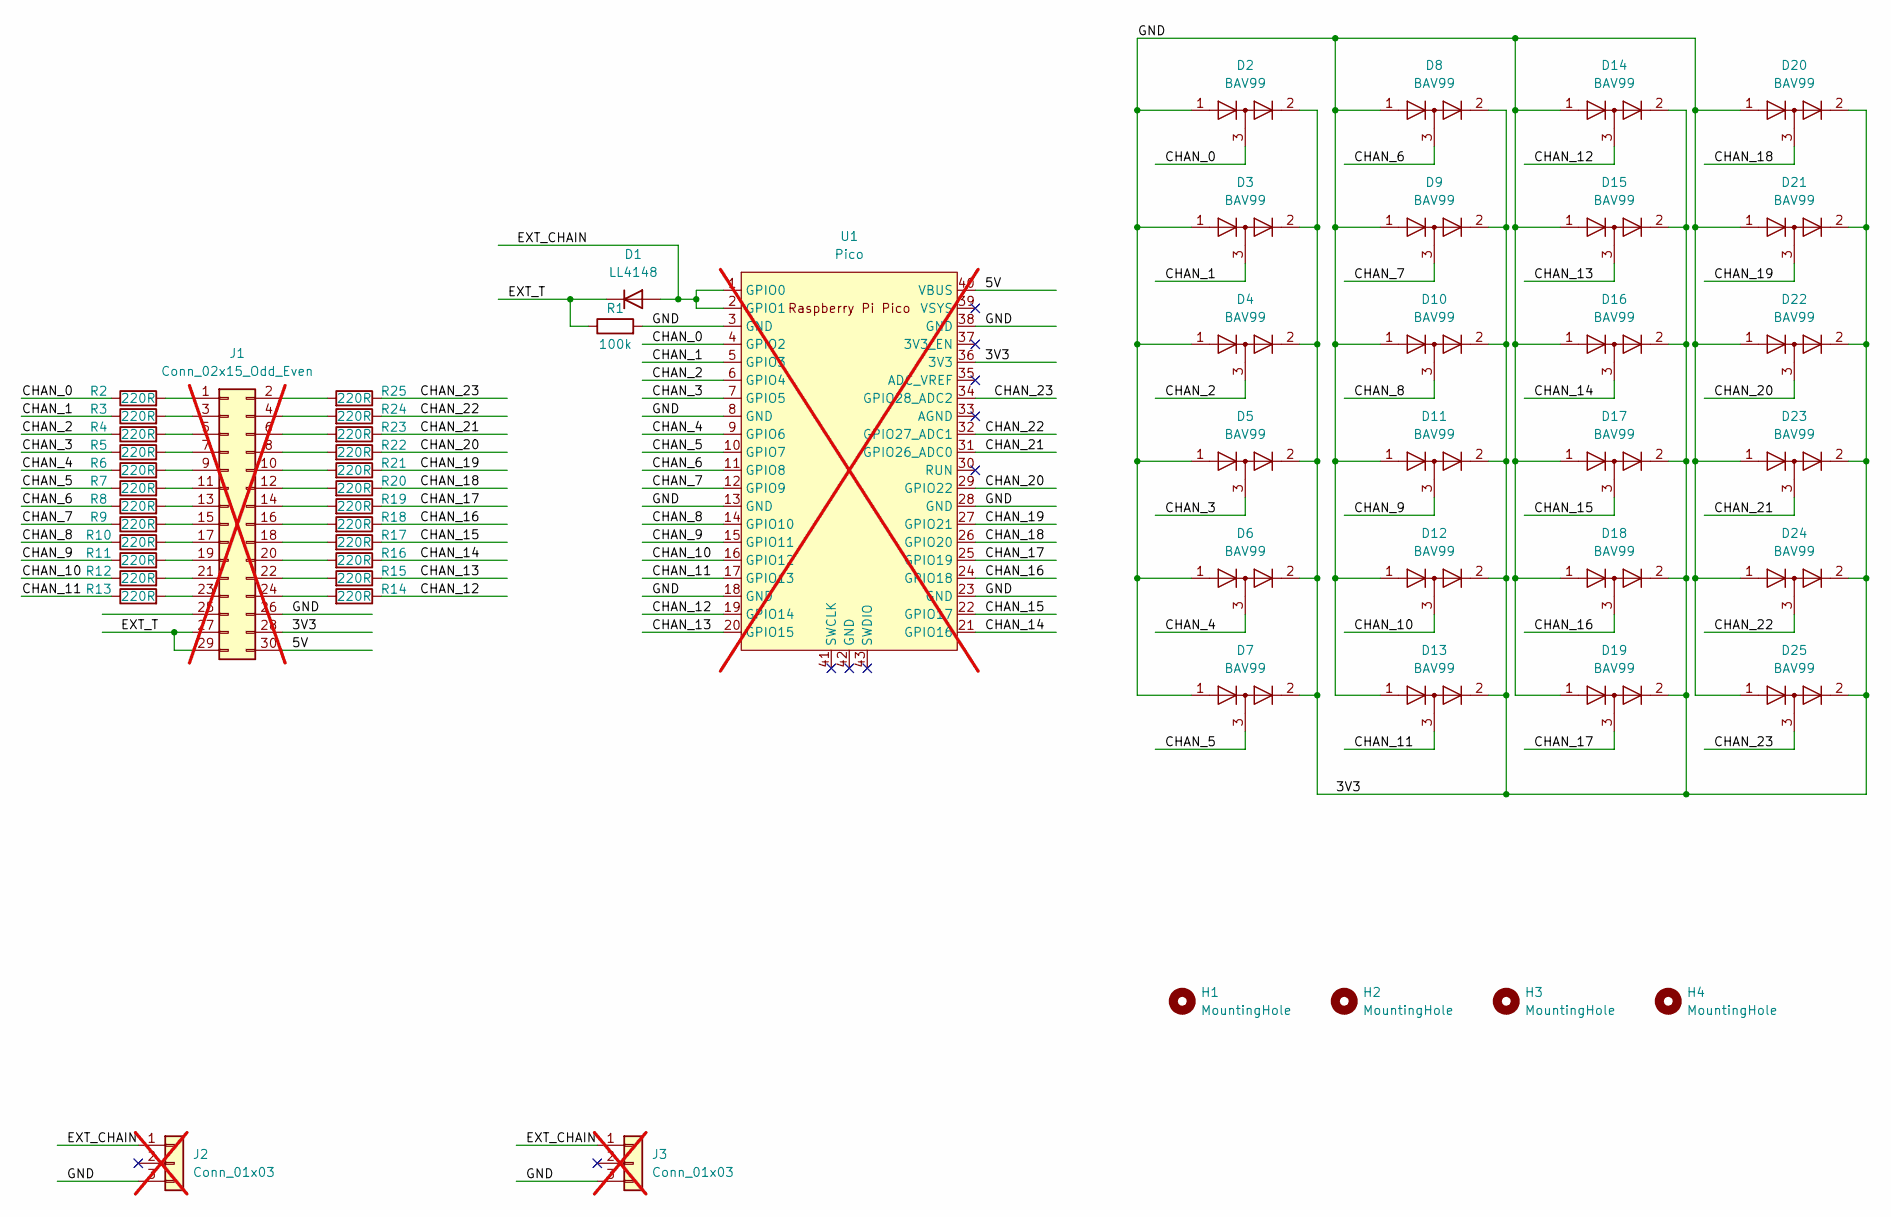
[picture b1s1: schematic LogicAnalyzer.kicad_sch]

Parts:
D1: LL4148; D_MiniMELF; LCSC Part # C5345986
D2, D3, D4, D5, D6, D7, D8, D9, D10, D11, D12, D13, D14, D15, D16, D17, D18, D19, D20, D21, D22, D23, D24, D25: BAV99; SOT-23; LCSC Part # C7420336
H1, H2, H3, H4: MountingHole; MountingHole_3.2mm_M3_DIN965
J1: Conn_02x15_Odd_Even; PinSocket_2x15_P2.54mm_Horizontal; not fitted
J2: Conn_01x03; PinSocket_1x03_P2.54mm_Horizontal; not fitted
J3: Conn_01x03; PinHeader_1x03_P2.54mm_Horizontal; not fitted
R1: 100k; R_0603_1608Metric; LCSC Part # C103211
R2, R3, R4, R5, R6, R7, R8, R9, R10, R11, R12, R13, R14, R15, R16, R17, R18, R19, R20, R21, R22, R23, R24, R25: 220R; R_0603_1608Metric; LCSC Part # C22962
U1: Pico; RPi_Pico_SMD_TH; not fitted

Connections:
/3V3: D2.2 (A), D3.2 (A), D4.2 (A), D5.2 (A), D6.2 (A), D7.2 (A), D8.2 (A), D9.2 (A), D10.2 (A), D11.2 (A), D12.2 (A), D13.2 (A), D14.2 (A), D15.2 (A), D16.2 (A), D17.2 (A), D18.2 (A), D19.2 (A), D20.2 (A), D21.2 (A), D22.2 (A), D23.2 (A), D24.2 (A), D25.2 (A), J1.28, U1.36 (3V3)
/5V: J1.30, U1.40 (VBUS)
/CHAN_0: D2.3 (K), R2.1, U1.4 (GPIO2)
/CHAN_1: D3.3 (K), R3.1, U1.5 (GPIO3)
/CHAN_2: D4.3 (K), R4.1, U1.6 (GPIO4)
/CHAN_3: D5.3 (K), R5.1, U1.7 (GPIO5)
/CHAN_4: D6.3 (K), R6.1, U1.9 (GPIO6)
/CHAN_5: D7.3 (K), R7.1, U1.10 (GPIO7)
/CHAN_6: D8.3 (K), R8.1, U1.11 (GPIO8)
/CHAN_7: D9.3 (K), R9.1, U1.12 (GPIO9)
/CHAN_8: D10.3 (K), R10.1, U1.14 (GPIO10)
/CHAN_9: D11.3 (K), R11.1, U1.15 (GPIO11)
/CHAN_10: D12.3 (K), R12.1, U1.16 (GPIO12)
/CHAN_11: D13.3 (K), R13.1, U1.17 (GPIO13)
/CHAN_12: D14.3 (K), R14.1, U1.19 (GPIO14)
/CHAN_13: D15.3 (K), R15.1, U1.20 (GPIO15)
/CHAN_14: D16.3 (K), R16.1, U1.21 (GPIO16)
/CHAN_15: D17.3 (K), R17.1, U1.22 (GPIO17)
/CHAN_16: D18.3 (K), R18.1, U1.24 (GPIO18)
/CHAN_17: D19.3 (K), R19.1, U1.25 (GPIO19)
/CHAN_18: D20.3 (K), R20.1, U1.26 (GPIO20)
/CHAN_19: D21.3 (K), R21.1, U1.27 (GPIO21)
/CHAN_20: D22.3 (K), R22.1, U1.29 (GPIO22)
/CHAN_21: D23.3 (K), R23.1, U1.31 (GPIO26_ADC0)
/CHAN_22: D24.3 (K), R24.1, U1.32 (GPIO27_ADC1)
/CHAN_23: D25.3 (K), R25.1, U1.34 (GPIO28_ADC2)
/EXT_CHAIN: D1.2 (A), J2.1, J3.1, U1.1 (GPIO0), U1.2 (GPIO1)
/EXT_T: D1.1 (K), J1.27, J1.29, R1.1
/GND: D2.1 (K), D3.1 (K), D4.1 (K), D5.1 (K), D6.1 (K), D7.1 (K), D8.1 (K), D9.1 (K), D10.1 (K), D11.1 (K), D12.1 (K), D13.1 (K), D14.1 (K), D15.1 (K), D16.1 (K), D17.1 (K), D18.1 (K), D19.1 (K), D20.1 (K), D21.1 (K), D22.1 (K), D23.1 (K), D24.1 (K), D25.1 (K), J1.26, J2.3, J3.3, R1.2, U1.3 (GND), U1.8 (GND), U1.13 (GND), U1.18 (GND), U1.23 (GND), U1.28 (GND), U1.38 (GND)
unnamed: J1.1, R2.2
unnamed: J1.2, R25.2
unnamed: J1.3, R3.2
unnamed: J1.4, R24.2
unnamed: J1.5, R4.2
unnamed: J1.6, R23.2
unnamed: J1.7, R5.2
unnamed: J1.8, R22.2
unnamed: J1.9, R6.2
unnamed: J1.10, R21.2
unnamed: J1.11, R7.2
unnamed: J1.12, R20.2
unnamed: J1.13, R8.2
unnamed: J1.14, R19.2
unnamed: J1.15, R9.2
unnamed: J1.16, R18.2
unnamed: J1.17, R10.2
unnamed: J1.18, R17.2
unnamed: J1.19, R11.2
unnamed: J1.20, R16.2
unnamed: J1.21, R12.2
unnamed: J1.22, R15.2
unnamed: J1.23, R13.2
unnamed: J1.24, R14.2

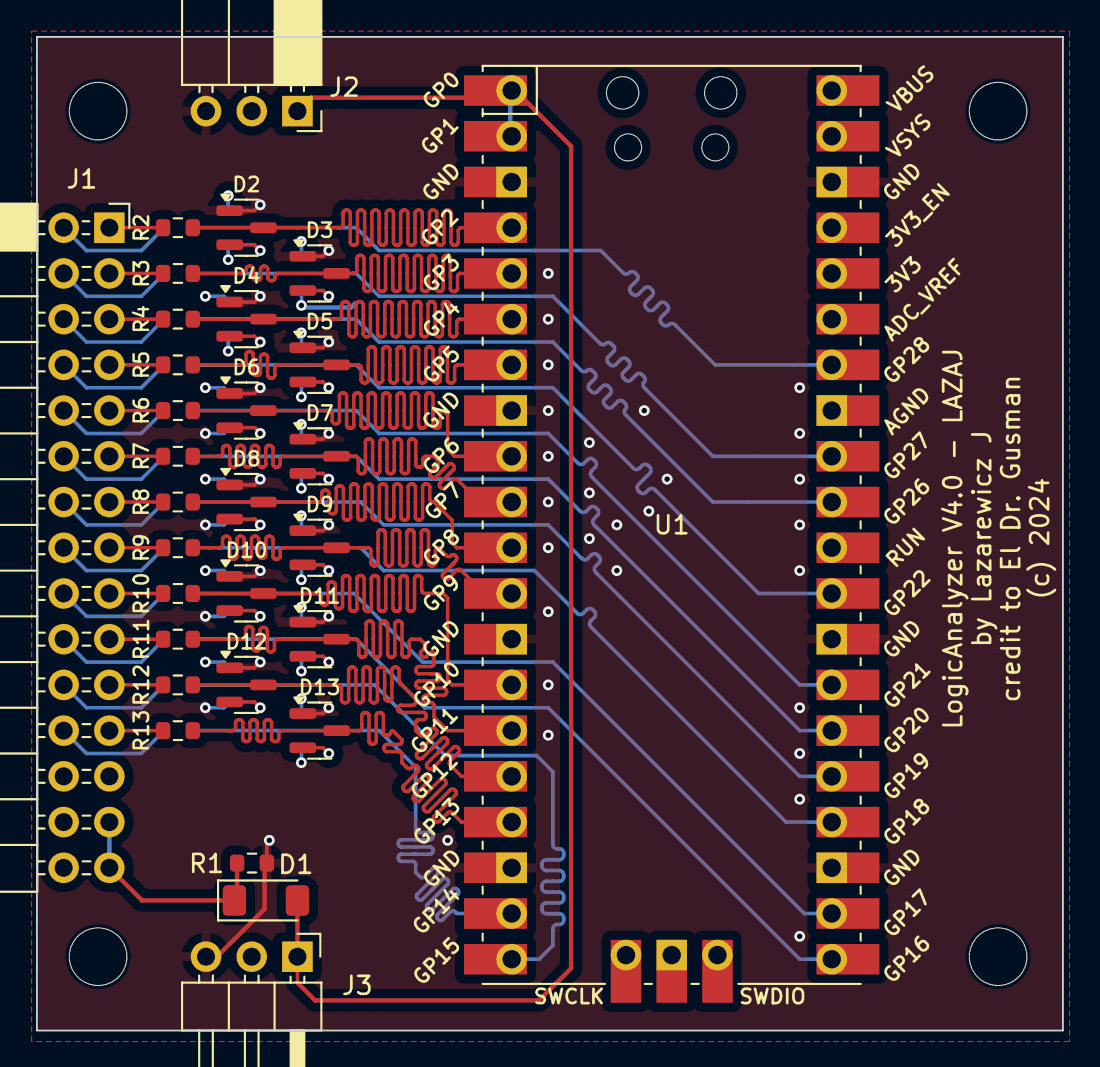
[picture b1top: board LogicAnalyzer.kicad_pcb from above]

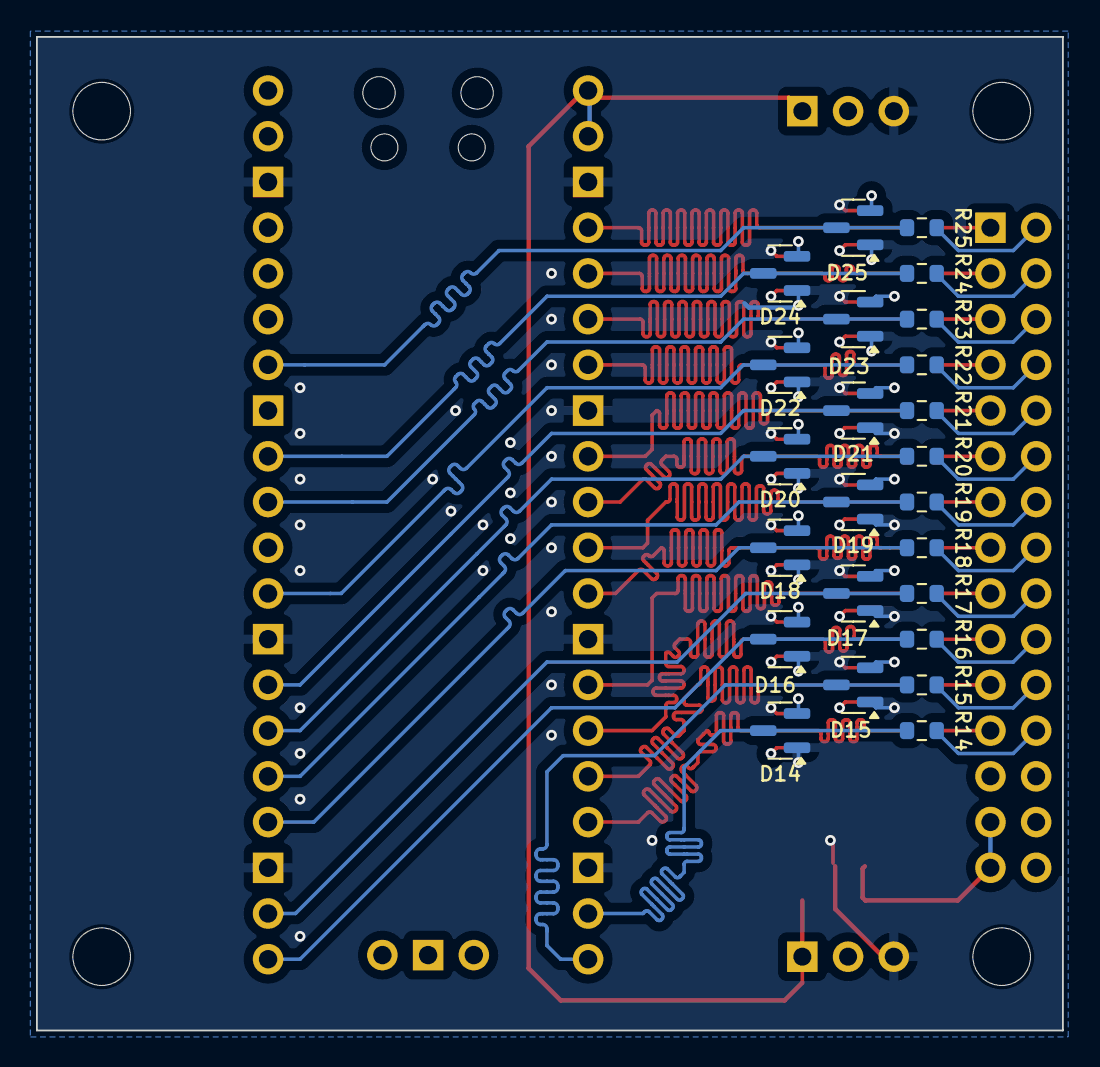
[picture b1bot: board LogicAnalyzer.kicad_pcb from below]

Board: 4 copper layers, 57.0 x 55.2 mm, 58 parts (24 on the bottom side), 53 nets.

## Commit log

2024-10-01 test commit
2024-10-01 undo test commit
2024-10-01 pcb: move designators to avoid silkscreen overlaps
2024-10-01 pcb: add track to avoid isolated copper fill island
2024-10-01 sch and pcb: add mountingholes to schematic and pcb to have parity
2024-10-01 add LCSC partnumbers, turn off refdes for mounting holes
2024-10-01 mounting holes: change to a footprint that has no electrical connection, pcb: make sure mounting holes are aligned horizontally and vertically
2024-10-01 add todo list
2024-10-03 created fabriaction outputs, saved KiCad project afterwards

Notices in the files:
Electronics/LogicAnalyzer/LogicAnalyzer-lazaj/LogicAnalyzer.kicad_pcb:
(c) 2024
